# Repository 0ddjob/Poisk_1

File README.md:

# Poisk 1
Information about the Ukrainian SSR IBM PC/XT compatible.

## [Analogue RGB to VGA Converter](/Poisk_1_RGB_DIN-to-VGA)
A simple board to convert the physical interface from a 7-pin DIN to standard VGA DE15 & 3.5mm sockets.<br>

- Pin 1 = red
- Pin 2 = GND
- Pin 3 = green
- Pin 4 = blue
- Pin 5 = composite sync.
- Pin 6 = audio
- Pin 7 = intensity

## [Monochrome Video to RCA Converter](/Poisk_1_Video_DIN-to-RCA)
A simple board to convert the physical interface from a 5-pin DIN to standard RCA sockets.<br>

- Pin 1 = audio
- Pin 2 = GND
- Pin 3 = +12V
- Pin 4 = +5V
- Pin 5 = video (monochrome)

## [Digital RGB to CGA/EGA Converter](/Poisk_1_SYNC_DIN-to-CGA)
A simple board to convert the physical interface from a 7-pin DIN to standard CGA/EGA DE9 socket.<br>

- Pin 1 = red
- Pin 2 = GND
- Pin 3 = green
- Pin 4 = blue
- Pin 5 = intensity
- Pin 6 = horizontal sync
- Pin 7 = vertical sync

## [Cassette to 3.5mm Audio Jack Converter](https://github.com/0ddjob/Conversion_Boards/tree/main/DIN-to-Audio_Jack)
A simple board to convert the physical interface from a 5-pin DIN to standard 3.5mm audio jacks.<br>

## [Datasheets](/Datasheets)
Relevant datasheets for parts used in the PCB designs.<br>

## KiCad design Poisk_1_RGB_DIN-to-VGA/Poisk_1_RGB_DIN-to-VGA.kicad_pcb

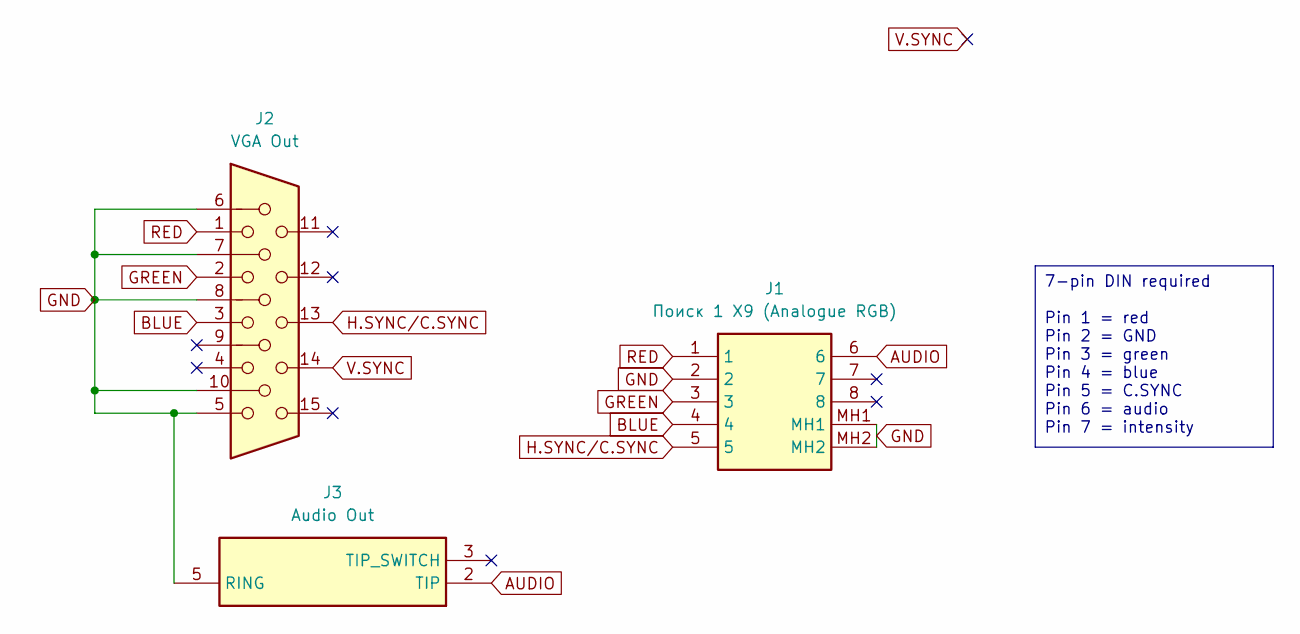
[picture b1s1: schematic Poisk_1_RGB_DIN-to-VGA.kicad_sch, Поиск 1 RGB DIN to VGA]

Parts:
J1: Поиск 1 X9 (Analogue RGB); 6710801; Manufacturer_Part_Number 671-0801
J2: VGA Out; DSUB-15-HD_Socket_Horizontal_P2.29x2.54mm_EdgePinOffset8.35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
J3: Audio Out; SJ3350820BTR; Mouser Part Number 179-SJ3-350820B-TR

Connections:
AUDIO: J1.6, J3.2 (TIP)
BLUE: J1.4, J2.3
GND: J1.2, J1.MH1, J1.MH2, J2.5, J2.6, J2.7, J2.8, J2.10, J3.5 (RING)
GREEN: J1.3, J2.2
H.SYNC/C.SYNC: J1.5, J2.13
RED: J1.1, J2.1
V.SYNC: J2.14

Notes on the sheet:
7-pin DIN required Pin 1 = red Pin 2 = GND Pin 3 = green Pin 4 = blue Pin 5 = C.SYNC Pin 6 = audio Pin 7 = intensity

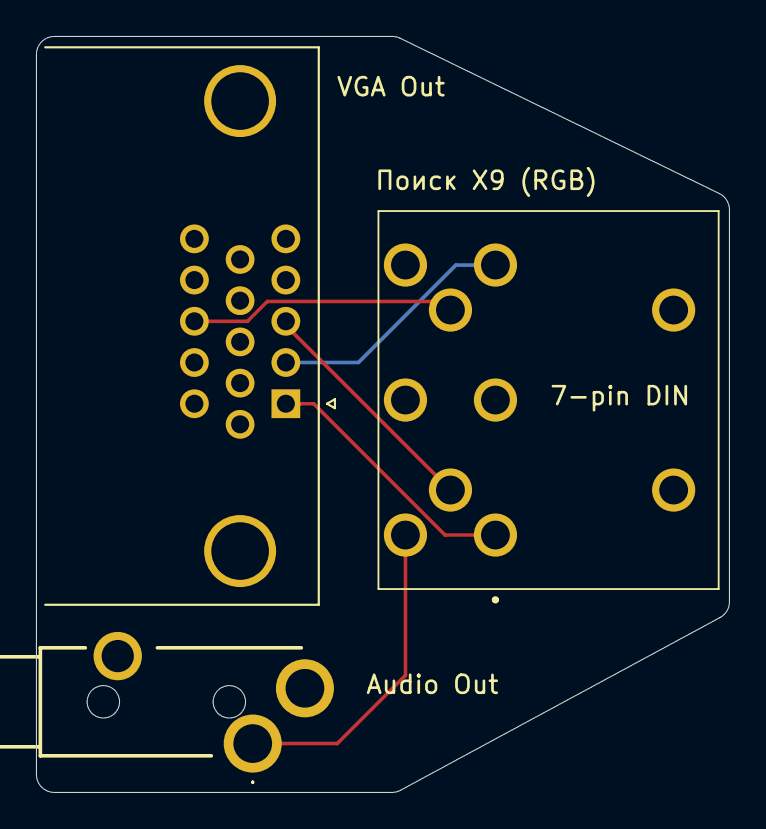
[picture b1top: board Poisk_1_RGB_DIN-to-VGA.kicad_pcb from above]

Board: 2 copper layers, 38.5 x 42.0 mm, 3 parts (0 on the bottom side), 6 nets.

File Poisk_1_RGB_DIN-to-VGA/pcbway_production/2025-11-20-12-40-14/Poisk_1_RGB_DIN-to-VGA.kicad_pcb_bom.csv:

Designator,Quantity,Value,Footprint,Package,MPN,DNP,Mount_Type,Description,Height,Manufacturer_Name,Mouser Part Number,Mouser Price/Stock
J1,1,Поиск 1 X9 (Analogue RGB),6710801,,671-0801,,tht,"Deltron 8 Pole Right Angle Din Socket Socket, 2A, 100 V ac, Lockable",19.5,DELTRON COMPONENTS,,
J2,1,VGA Out,DSUB-15-HD_Socket_Horizontal_P2.29x2.54mm_EdgePinOffset8.35mm_Housed_MountingHolesOffset10.89mm,,,,tht,"15-pin D-SUB connector, socket (female), High density (3 columns), Triple Row, Generic, VGA-connector",,,,
J3,1,Audio Out,SJ3350820BTR,,SJ3-350820B-TR,,tht,"3.5 mm Stereo Jack, Through Hole, 2 Conductors, 1 Internal Switches,  Tape & Reel Packaging",5.3,Same Sky,179-SJ3-350820B-TR,https://www.mouser.co.uk/ProductDetail/Same-Sky/SJ3-350820B-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

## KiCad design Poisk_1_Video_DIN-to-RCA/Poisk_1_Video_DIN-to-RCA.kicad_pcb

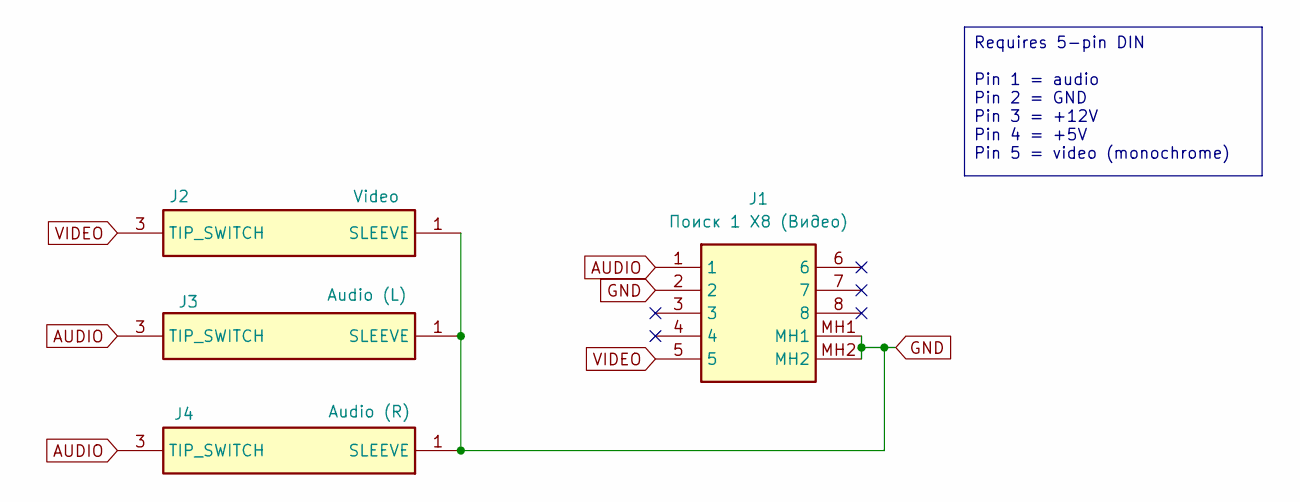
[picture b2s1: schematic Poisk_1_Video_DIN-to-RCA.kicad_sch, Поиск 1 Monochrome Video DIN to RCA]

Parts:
J1: Поиск 1 X8 (Видео); 6710801; Manufacturer_Part_Number 671-0801
J2: Video; FC68371; Manufacturer_Part_Number FC68371
J3: Audio (L); FC68371; Manufacturer_Part_Number FC68371
J4: Audio (R); FC68371; Manufacturer_Part_Number FC68371

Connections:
AUDIO: J1.1, J3.3 (TIP_SWITCH), J4.3 (TIP_SWITCH)
GND: J1.2, J1.MH1, J1.MH2, J2.1 (SLEEVE), J3.1 (SLEEVE), J4.1 (SLEEVE)
VIDEO: J1.5, J2.3 (TIP_SWITCH)

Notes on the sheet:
Requires 5-pin DIN Pin 1 = audio Pin 2 = GND Pin 3 = +12V Pin 4 = +5V Pin 5 = video (monochrome)

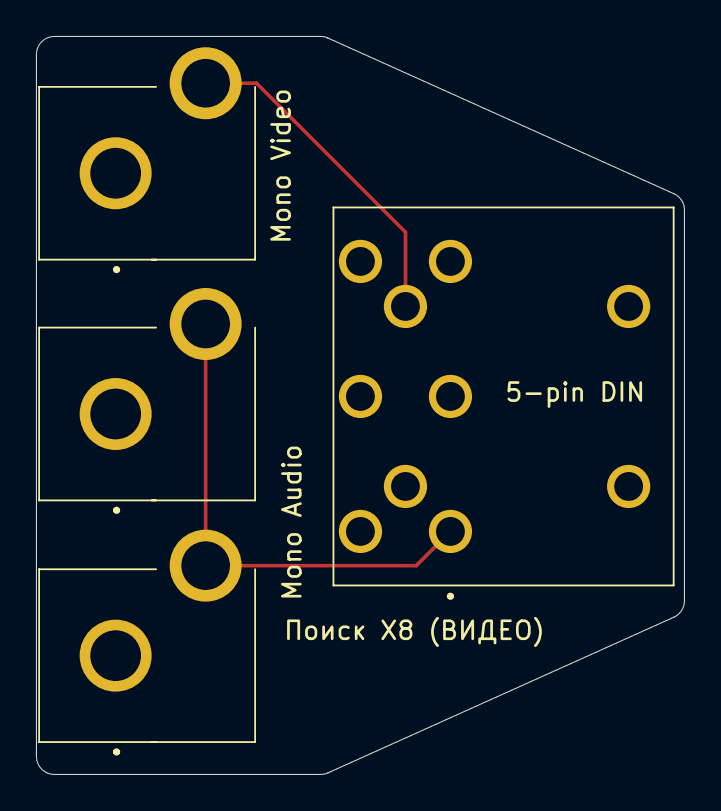
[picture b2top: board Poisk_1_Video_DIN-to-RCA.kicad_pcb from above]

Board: 2 copper layers, 36.0 x 41.0 mm, 4 parts (0 on the bottom side), 3 nets.

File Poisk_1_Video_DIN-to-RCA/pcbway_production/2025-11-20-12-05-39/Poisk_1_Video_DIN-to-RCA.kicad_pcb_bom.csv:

Designator,Quantity,Value,Footprint,Package,MPN,DNP,Mount_Type,Description,Height,Manufacturer_Name
J1,1,Поиск 1 X8 (Видео),6710801,,671-0801,,tht,"Deltron 8 Pole Right Angle Din Socket Socket, 2A, 100 V ac, Lockable",19.5,DELTRON COMPONENTS
J2,1,Video,FC68371,,FC68371,,tht,Socket; RCA; female; angled 90; THT; nickel plated; Marker: black,14,CLIFF ELECTRONIC COMPONENTS
J3,1,Audio (L),FC68371,,FC68371,,tht,Socket; RCA; female; angled 90; THT; nickel plated; Marker: black,14,CLIFF ELECTRONIC COMPONENTS
J4,1,Audio (R),FC68371,,FC68371,,tht,Socket; RCA; female; angled 90; THT; nickel plated; Marker: black,14,CLIFF ELECTRONIC COMPONENTS
